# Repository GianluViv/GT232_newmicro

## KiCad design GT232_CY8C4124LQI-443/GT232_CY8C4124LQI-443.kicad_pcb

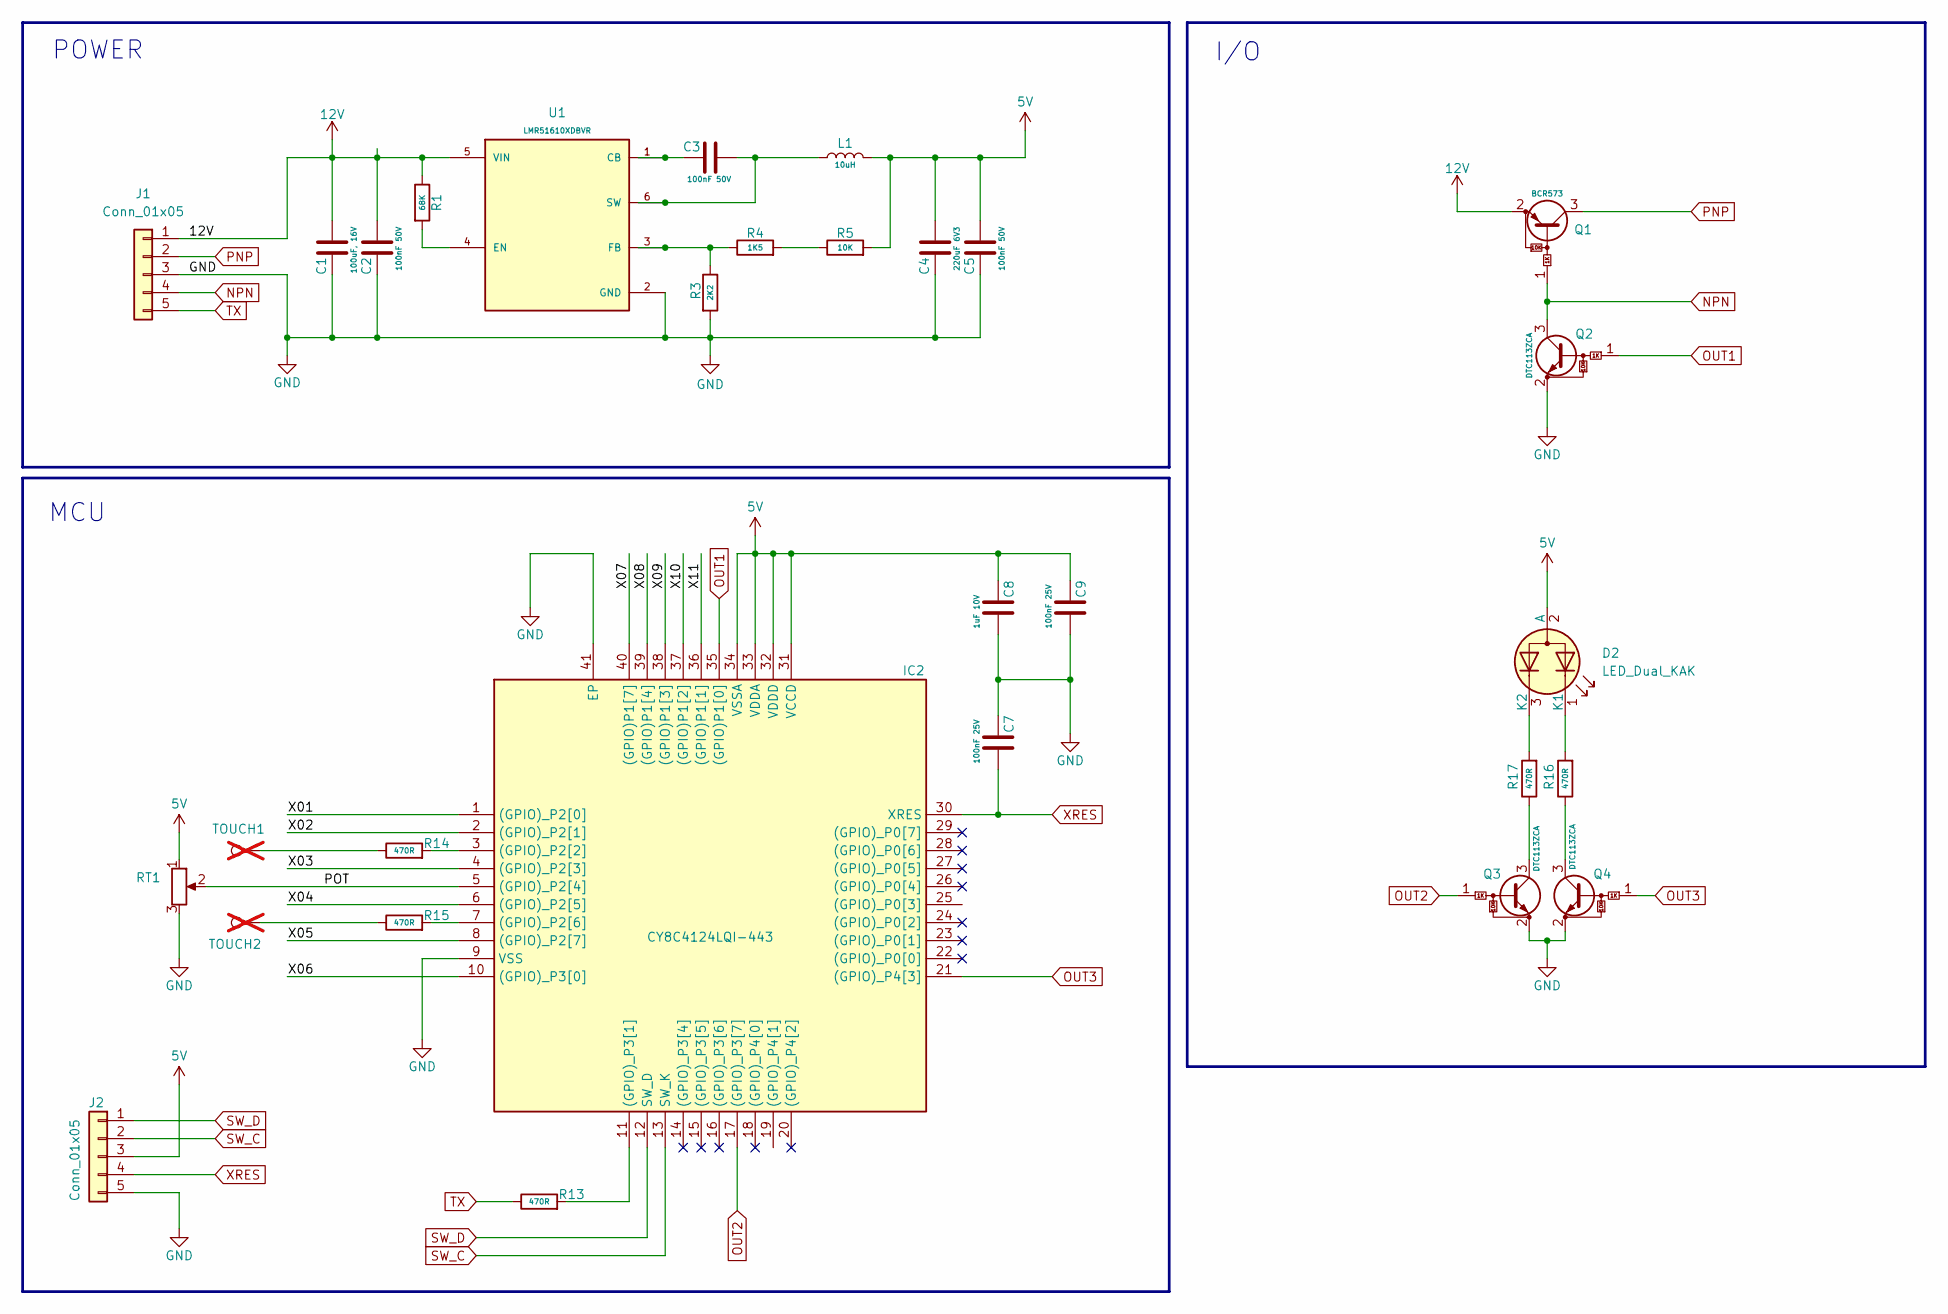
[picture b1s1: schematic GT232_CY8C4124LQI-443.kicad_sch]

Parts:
C1: 100uF, 16V; C_1210_3225Metric_Pad1.33x2.70mm_HandSolder
C2: 100nF 50V; C_0805_2012Metric_Pad1.18x1.45mm_HandSolder
C3: 100nF 50V; C_0603_1608Metric_Pad1.08x0.95mm_HandSolder
C4: 220uF 6V3; C_1210_3225Metric_Pad1.33x2.70mm_HandSolder
C5: 100nF 50V; C_1206_3216Metric_Pad1.33x1.80mm_HandSolder
C7, C9: 100nF 25V; C_0603_1608Metric
C8: 1uF 10V; C_0603_1608Metric
D2: LED_Dual_KAK; LED_LiteOn_LTST-S326
IC2: CY8C4124LQI-443; QFN50P600X600X60-41N-D; Mouser Part Number 727-CY8C4124LQI-443
J1: Conn_01x05; PinHeader_1x05_P2.54mm_Vertical
J2: Conn_01x05; Harwin_M20-89005xx_1x05_P2.54mm_Horizontal
L1: 10uH; L_Wurth_WE-LQSH-3012
Q1: BCR573; SOT-23
Q2, Q3, Q4: DTC113ZCA; SOT-23
R1: 68K; R_0603_1608Metric_Pad0.98x0.95mm_HandSolder
R3: 2K2; R_0603_1608Metric_Pad0.98x0.95mm_HandSolder
R4: 1K5; R_0603_1608Metric_Pad0.98x0.95mm_HandSolder
R5: 10K; R_0603_1608Metric_Pad0.98x0.95mm_HandSolder
R13, R14, R15, R16, R17: 470R; R_0603_1608Metric
RT1: R_Potentiometer
TOUCH1, TOUCH2: TestPoint; TestPoint_Loop_D2.50mm_Drill1.0mm; not fitted
U1: LMR51610XDBVR; SOT-23-6; PARTREV B

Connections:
5V: C4.2, C5.2, C8.1, C9.1, D2.2 (A), IC2.31 (VCCD), IC2.32 (VDDD), IC2.33 (VDDA), IC2.34 (VSSA), J2.3, L1.2, R5.2, RT1.1
12V: C1.2, C2.2, J1.1, Q1.2 (E), R1.1, U1.5 (VIN)
/POT: IC2.5 ((GPIO)_P2[4]), RT1.2
/X01: IC2.1 ((GPIO)_P2[0])
/X02: IC2.2 ((GPIO)_P2[1])
/X03: IC2.4 ((GPIO)_P2[3])
/X04: IC2.6 ((GPIO)_P2[5])
/X05: IC2.8 ((GPIO)_P2[7])
/X06: IC2.10 ((GPIO)_P3[0])
/X07: IC2.40 ((GPIO)P1[7])
/X08: IC2.39 ((GPIO)P1[4])
/X09: IC2.38 ((GPIO)P1[3])
/X10: IC2.37 ((GPIO)P1[2])
/X11: IC2.36 ((GPIO)P1[1])
GND: C1.1, C2.1, C4.1, C5.1, C7.1, C8.2, C9.2, IC2.9 (VSS), IC2.41 (EP), J1.3, J2.5, Q2.2 (E), Q3.2 (E), Q4.2 (E), R3.2, RT1.3, U1.2 (GND)
NPN: J1.4, Q1.1 (B), Q2.3 (C)
unnamed: D2.1 (K1), R16.2
unnamed: D2.3 (K2), R17.2
unnamed: IC2.3 ((GPIO)_P2[2]), R14.2
unnamed: IC2.7 ((GPIO)_P2[6]), R15.2
unnamed: IC2.11 ((GPIO)_P3[1]), R13.2
unnamed: Q3.3 (C), R17.1
unnamed: Q4.3 (C), R16.1
unnamed: R4.2, R5.1
unnamed: R14.1, TOUCH1.1 (1_1)
unnamed: R15.1, TOUCH2.1 (1_1)
unnamed: C3.1, U1.1 (CB)
unnamed: R1.2, U1.4 (EN)
unnamed: R3.1, R4.1, U1.3 (FB)
unnamed: C3.2, L1.1, U1.6 (SW)
OUT1: IC2.35 ((GPIO)P1[0]), Q2.1 (B)
OUT2: IC2.17 ((GPIO)_P3[7]), Q3.1 (B)
OUT3: IC2.21 ((GPIO)_P4[3]), Q4.1 (B)
PNP: J1.2, Q1.3 (C)
SW_C: IC2.13 (SW_K), J2.2
SW_D: IC2.12 (SW_D), J2.1
TX: J1.5, R13.1
XRES: C7.2, IC2.30 (XRES), J2.4

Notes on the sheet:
POWER
I/O
MCU

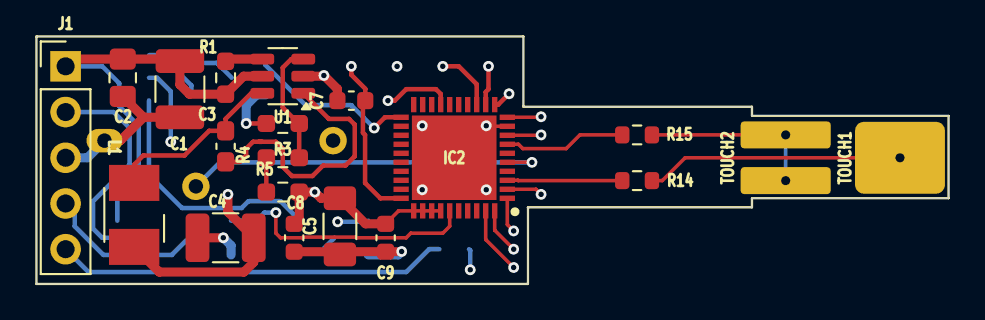
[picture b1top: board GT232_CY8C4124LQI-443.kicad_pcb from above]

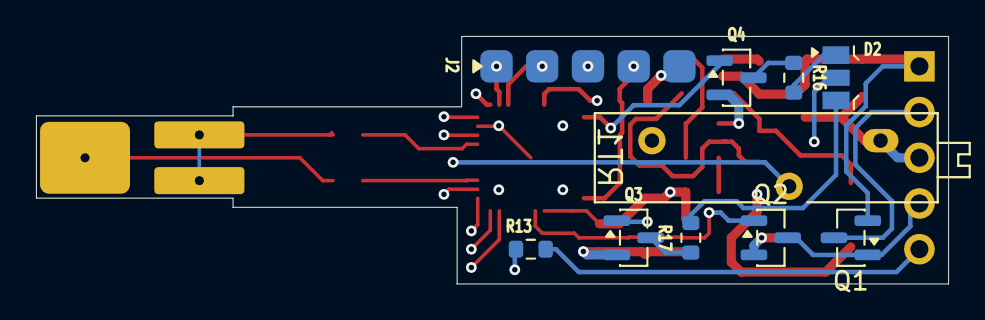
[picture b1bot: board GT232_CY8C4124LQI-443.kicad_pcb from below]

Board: 4 copper layers, 50.7 x 13.8 mm, 31 parts (10 on the bottom side), 27 nets.

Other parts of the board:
TOUCH2#2: TestPoint; TestPoint_Loop_D2.50mm_Drill1.0mm

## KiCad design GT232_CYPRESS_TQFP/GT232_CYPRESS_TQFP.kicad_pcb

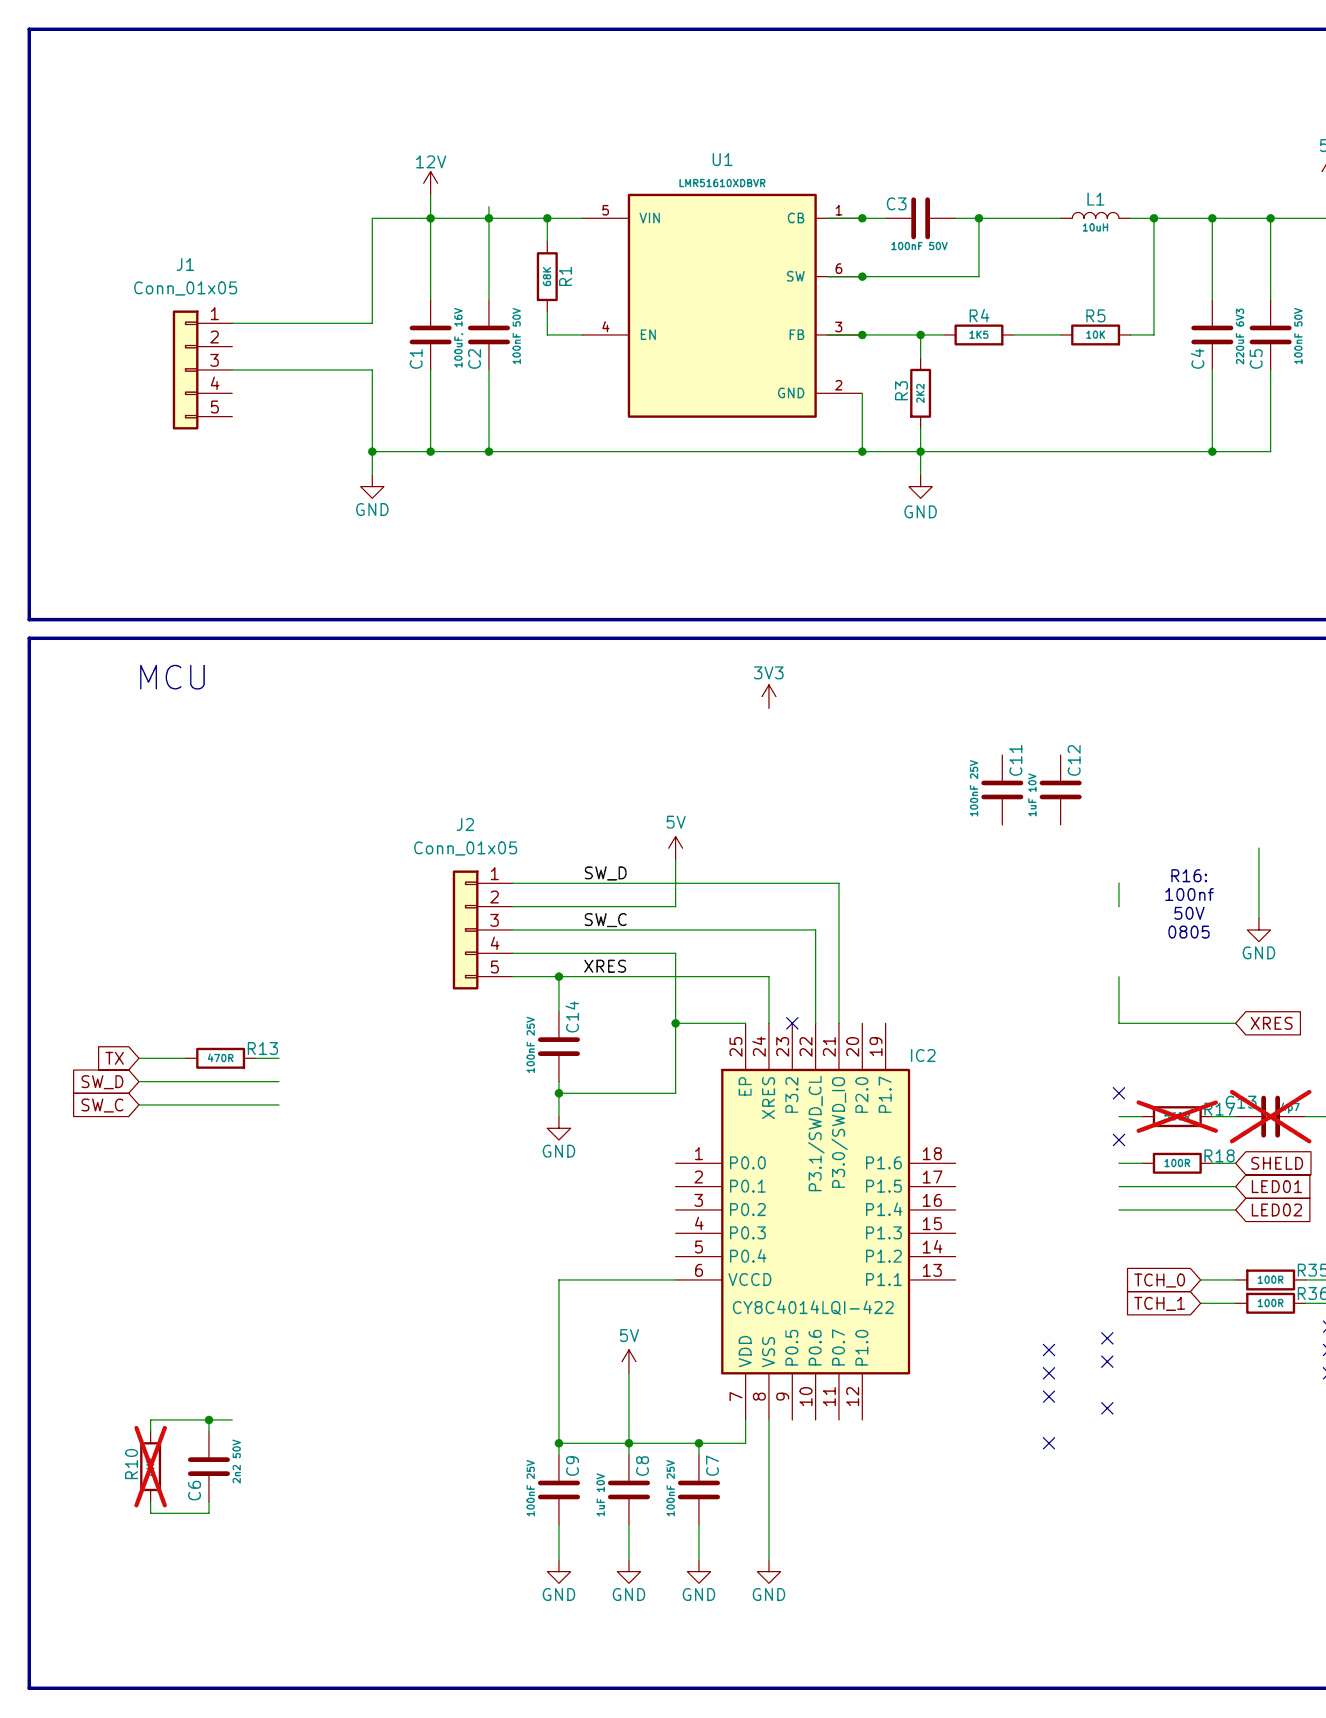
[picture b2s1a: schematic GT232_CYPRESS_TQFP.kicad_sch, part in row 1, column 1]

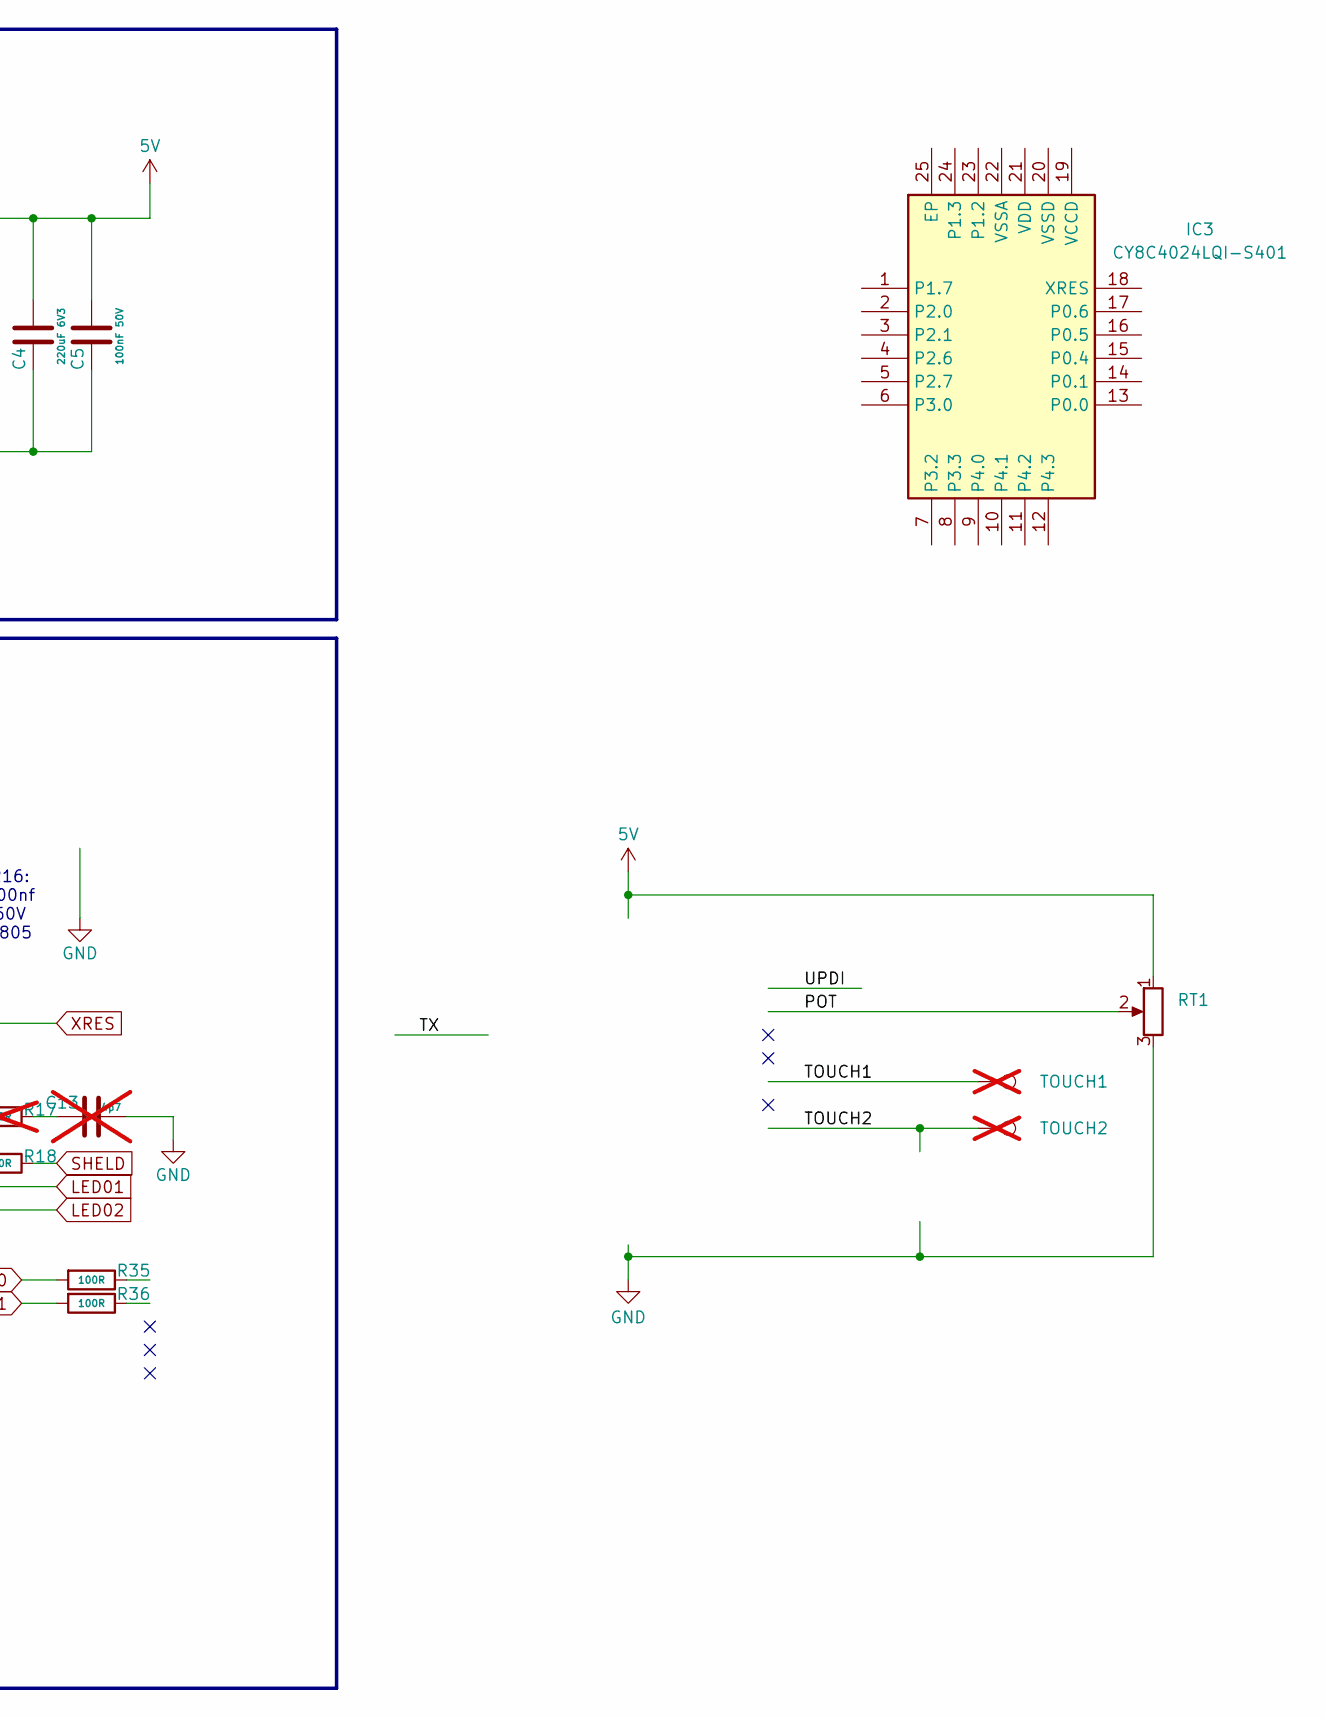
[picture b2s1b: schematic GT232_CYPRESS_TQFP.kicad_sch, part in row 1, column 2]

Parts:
C1: 100uF, 16V; C_1210_3225Metric_Pad1.33x2.70mm_HandSolder
C2: 100nF 50V; C_0805_2012Metric_Pad1.18x1.45mm_HandSolder
C3: 100nF 50V; C_0603_1608Metric_Pad1.08x0.95mm_HandSolder
C4: 220uF 6V3; C_1210_3225Metric_Pad1.33x2.70mm_HandSolder
C5: 100nF 50V; C_1206_3216Metric_Pad1.33x1.80mm_HandSolder
C6: 2n2 50V; C_0805_2012Metric
C7, C9, C11, C14: 100nF 25V; C_0603_1608Metric
C8, C12: 1uF 10V; C_0603_1608Metric
C13: 4p7; C_0805_2012Metric; not fitted
IC2: CY8C4014LQI-422; QFN50P400X400X60-25N-D; Manufacturer_Part_Number CY8C4014LQI-422; Mouser Part Number 727-CY8C4014LQI-422
IC3: CY8C4024LQI-S401; QFN50P400X400X60-25N-D; Mouser Part Number 727-CY8C4024LQI-S401
J1, J2: Conn_01x05; PinHeader_1x05_P2.54mm_Vertical
L1: 10uH; L_Wurth_WE-LQSH-3012
R1: 68K; R_0603_1608Metric_Pad0.98x0.95mm_HandSolder
R3: 2K2; R_0603_1608Metric_Pad0.98x0.95mm_HandSolder
R4: 1K5; R_0603_1608Metric_Pad0.98x0.95mm_HandSolder
R5: 10K; R_0603_1608Metric_Pad0.98x0.95mm_HandSolder
R10: 4K7; R_0805_2012Metric; not fitted
R13: 470R; R_0603_1608Metric
R17: 560R; R_0805_2012Metric; not fitted
R18, R35, R36: 100R; R_0603_1608Metric
RT1: R_Potentiometer
TOUCH1, TOUCH2: TestPoint; TestPoint_Loop_D2.50mm_Drill1.0mm; not fitted
U1: LMR51610XDBVR; SOT-23-6; PARTREV B

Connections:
5V: C4.2, C5.2, C7.1, C8.1, C9.1, IC2.6 (VCCD), IC2.7 (VDD), J2.2, L1.2, R5.2, RT1.1
12V: C1.2, C2.2, J1.1, R1.1, U1.5 (VIN)
/POT: RT1.2
/TOUCH1: TOUCH1.1 (1_1)
/TOUCH2: TOUCH2.1 (1_1); also elsewhere on the board
GND: C1.1, C2.1, C4.1, C5.1, C7.2, C8.2, C9.2, C13.2, C14.2, IC2.8 (VSS), IC2.25 (EP), J1.3, J2.4, R3.2, RT1.3, U1.2 (GND)
unnamed: C6.1, R10.1
unnamed: C6.2, R10.2
unnamed: C13.1, R17.1
unnamed: R4.2, R5.1
unnamed: C3.1, U1.1 (CB)
unnamed: R1.2, U1.4 (EN)
unnamed: R3.1, R4.1, U1.3 (FB)
unnamed: C3.2, L1.1, U1.6 (SW)
SHELD: R18.1
SW_C: IC2.22 (P3.1/SWD_CL), J2.3
SW_D: IC2.21 (P3.0/SWD_IO), J2.1
TCH_0: R35.2
TCH_1: R36.2
TX: R13.1
XRES: C14.1, IC2.24 (XRES), J2.5

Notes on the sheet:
R16: 100nf 50V 0805
MCU

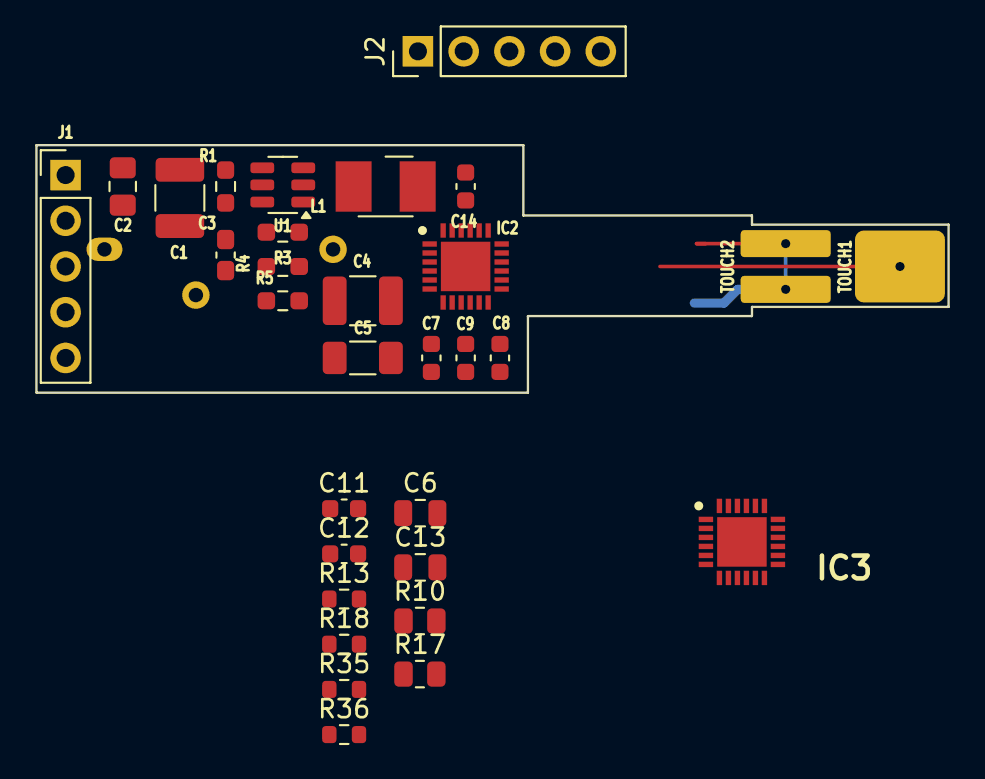
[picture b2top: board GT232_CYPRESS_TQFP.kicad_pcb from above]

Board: 2 copper layers, 50.7 x 13.8 mm, 33 parts (1 on the bottom side), 15 nets.

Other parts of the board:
TOUCH2#2: TestPoint; TestPoint_Loop_D2.50mm_Drill1.0mm

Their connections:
/TOUCH2: TOUCH2#2.1; also elsewhere on the board

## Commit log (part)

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2026-04-25 Aggiornato schema e PCB del modello con micro 4014
2026-04-26 eliminati micro non adatti, terminato lo schema e sbroglio PCB
